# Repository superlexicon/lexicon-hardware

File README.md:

# Lexicon Hardware, Radio Firmware & Device Drivers

> 🌐 **Full Interactive Presentation, Hardware Ecosystem & Live Testnet Telemetry: [www.superlexicon.com](https://www.superlexicon.com)**

Unified open-hardware repository containing the radio transceiver firmware, Linux/RT-Smart device drivers, 3D enclosures, and reference hardware designs for the **Lexicon** radio-native blockchain ecosystem.

---

## Repository Structure

```text
lexicon-hardware/
├── firmware/
│   ├── nrf54l15-lr2021/          # Device 1: Seeed Studio XIAO nRF54L15 + LR2021 Eval Kit (Zephyr RTOS)
│   └── am36-lr2021/              # Device 2: Lierda AM36-Pico ESP32-S3 + LR2021 USB Dongle (ESP-IDF + 3D Enclosure)
├── drivers/
│   └── k230-lr2021-radio/        # Device 3: LilyGO T-Display K230 RISC-V SPI Radio Service & Host Daemon
└── designs/
    └── lexicon-dual-rf-dongle/   # Turnkey EMS Reference Design: Dual-LR2021 USB Dongle (Schematics, Gerber, BOM, 3D CAD)
```

---

## Supported Hardware Targets

| Target Device | MCU / SoC | Radio Transceiver | Stack | Directory |
| :--- | :--- | :--- | :--- | :--- |
| **Seeed Studio LR2021 LoRa Plus Eval Kit** | Nordic `nRF54L15` (Cortex-M33) | Semtech `LR2021` (915 MHz / 2.4 GHz FLRC) | Zephyr RTOS | [`firmware/nrf54l15-lr2021/`](./firmware/nrf54l15-lr2021/) |
| **Lierda AM36-Pico (`L-LRMAM36-FANN4-PK02`)** | Espressif `ESP32-S3` (Dual Xtensa LX7) | Semtech `LR2021` (Sub-GHz / 2.4 GHz FLRC) | ESP-IDF v5.x | [`firmware/am36-lr2021/`](./firmware/am36-lr2021/) |
| **LilyGO T-Display K230 Kit** | Canaan `Kendryte K230` (Dual RISC-V C908) | Semtech `LR2021` (SPI Daughterboard) | RT-Smart / Linux C | [`drivers/k230-lr2021-radio/`](./drivers/k230-lr2021-radio/) |
| **Lexicon Dual-RF USB Dongle (Reference)** | `ESP32-S3` + Dual `LR2021` | 2x Parallel `LR2021` (`RF0` + `RF1`) | Turnkey EMS Package | [`designs/lexicon-dual-rf-dongle/`](./designs/lexicon-dual-rf-dongle/) |

---

## Common FLRC Air & Serial Protocol

All three hardware targets implement the Lexicon **Phase-C FLRC Burst Protocol**:
- **Modulation:** Semtech `LR2021` FLRC up to **2.6 Mbps** raw air data rate (`511 B` physical frames / `495 B` payload chunks, `220 µs` interframe pacing).
- **Reassembly Capacity:** Up to **64 KB (`65,024 B` / 132 packets)** per burst with per-burst random IDs and 4 concurrent reassembly slots.
- **Host Serial / IPC Interface:** Dedicated control lane (`'G'`, `'T'`, `'R'`, `'C'`, `'W'`, `'S'`, `'Q'`) ensuring TX terminal notifications are never dropped under payload ring pressure.

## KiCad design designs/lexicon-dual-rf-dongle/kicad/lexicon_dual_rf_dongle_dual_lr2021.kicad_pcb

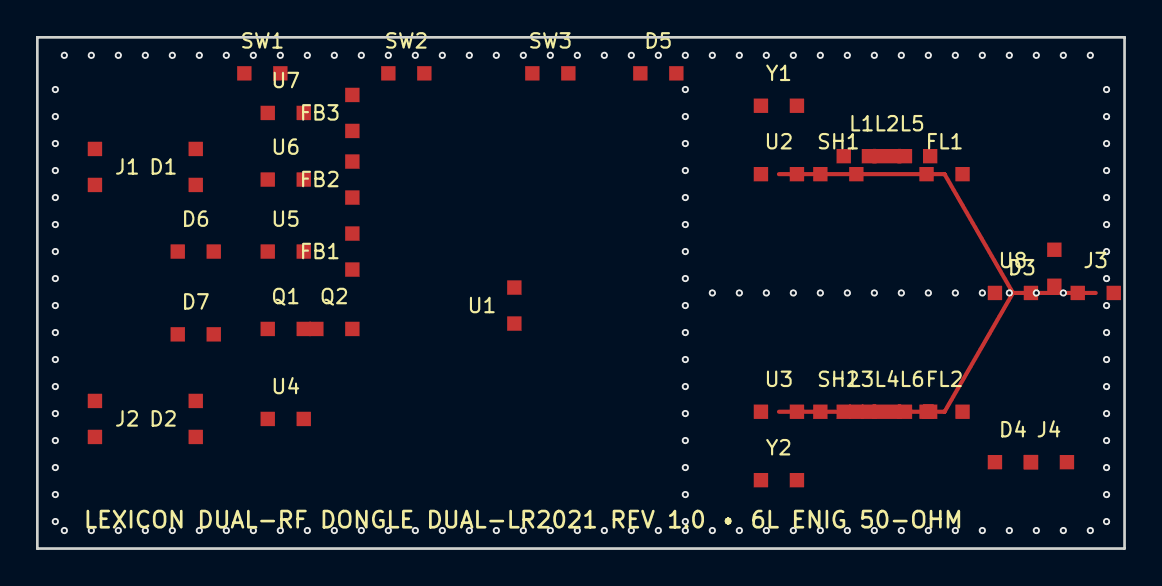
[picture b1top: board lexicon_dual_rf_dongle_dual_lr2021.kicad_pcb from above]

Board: 6 copper layers, 60.4 x 28.4 mm, 39 parts (0 on the bottom side), 2 nets.

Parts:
D1, D2: USBLC6-2SC6; SOT-23-6
D3: RClamp0521P_SMA; SLP1006P2_0402
D4: RClamp0521P_UFL; SLP1006P2_0402
D5: WS2812B-2020; LED-SMD-2020_4P
D6, D7: B5819WSL; SOD-123FL
FB1, FB2, FB3: BLM18PG121SN1D; 0603
FL1: TA0632A_915MHz_SAW; SMD-1411_5P
FL2: LFD18868M_918MHz_2G4; SMD-1608_6P
J1: USB-C-16P-NATIVE; USB-C-SMD-16P-H3.16
J2: USB-C-16P-UART; USB-C-SMD-16P-H3.16
J3: SMA-EDGE-50OHM; SMA-EDGE-LAUNCH-1.6MM
J4: U.FL-R-SMT-1; U.FL-SMD-3P
L1, L2: 12nH_RF0; 0402
L3, L4: 12nH_RF1; 0402
L5: 6.8nH_RF0; 0402
L6: 6.8nH_RF1; 0402
Q1, Q2: UMH3N; SOT-363_SC-70-6
SH1: RF-SHIELD-RF0; SHIELD-CAN-16x11MM
SH2: RF-SHIELD-RF1; SHIELD-CAN-16x11MM
SW1: PTS636-RST; SW-SMD-6.0x3.5mm
SW2: PTS636-BOOT; SW-SMD-6.0x3.5mm
SW3: PTS636-KEY; SW-SMD-6.0x3.5mm
U1: ESP32-S3-WROOM-1-N16R8; MODULE_ESP32-S3-WROOM-1
U2: LR2021IMLTRT_RF0; VQFN-32-EP_5x5mm_P0.5mm
U3: LR2021IMLTRT_RF1; VQFN-32-EP_5x5mm_P0.5mm
U4: CP2102N-A02-GQFN28; QFN-28-EP_5x5mm_P0.5mm
U5: RT9080-33GJ5_DIG; SOT-23-5
U6: RT9080-33GJ5_RF0; SOT-23-5
U7: RT9080-33GJ5_RF1; SOT-23-5
U8: SKY13373-460LF; QFN-12_2x2mm
Y1: 32.000MHz_TCXO_0; SMD-2016_4P
Y2: 32.000MHz_TCXO_1; SMD-2016_4P

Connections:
+3V3_DIG: D1.2, D2.2, D3.2, D4.2, D5.2, D6.2, D7.2, FB1.2, FB2.2, FB3.2, FL1.2, FL2.2, J1.2, J2.2, J3.2, J4.2, L1.2, L2.2, L3.2, L4.2, L5.2, L6.2, Q1.2, Q2.2, SH1.2, SH2.2, SW1.2, SW2.2, SW3.2, U1.2, U2.2, U3.2, U4.2, U5.2, U6.2, U7.2, U8.2, Y1.2, Y2.2
GND: D1.1, D2.1, D3.1, D4.1, D5.1, D6.1, D7.1, FB1.1, FB2.1, FB3.1, FL1.1, FL2.1, J1.1, J2.1, J3.1, J4.1, L1.1, L2.1, L3.1, L4.1, L5.1, L6.1, Q1.1, Q2.1, SH1.1, SH2.1, SW1.1, SW2.1, SW3.1, U1.1, U2.1, U3.1, U4.1, U5.1, U6.1, U7.1, U8.1, Y1.1, Y2.1
